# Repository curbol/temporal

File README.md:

# Temporal

A 36-42 key split ergonomic keyboard with wireless support, a breakoff pinky column, and optional encoders in the thumb cluster.

## Design

### Layout

- 36-42 keys depending on configuration:
  - 42/41/40 keys (0/1/2 encoders) with full pinky column
  - 38/37/36 keys (0/1/2 encoders) with breakoff pinky column
- Column stagger and splay on pinky and ring columns

### Hardware

- Kailh Choc v1 or v2 low-profile switches, with optional hotswap sockets
- nice!nano or other Pro Micro compatible microcontrollers
- Optional nice!view display
- Optional EC11/EC12 rotary encoders in thumb cluster (up to 2)
- Wireless with battery support
- Reversible PCB
- 3D-printable cases, with an optional kickstand for tenting

### Tools

- [Ergogen](https://ergogen.ceoloide.com/) generates the layout, PCB, plates, and cases from [ergogen/config.yaml](ergogen/config.yaml)
- [KiCad](https://www.kicad.org/) v10 holds the hand-routed traces; its `pcbnew` API and `kicad-cli` drive the scripted post-processing and the exports

## Firmware

Temporal runs [ZMK](https://zmk.dev/). The shield definition and default keymap live in [temporal-zmk](https://github.com/curbol/temporal-zmk); [curbol/zmk-config](https://github.com/curbol/zmk-config) is a working config that uses it.

## Build Guide

[docs/build-guide.md](docs/build-guide.md) covers assembly and ordering. [docs/bom.md](docs/bom.md) lists every component a full build needs.

## Keycaps

Any Choc-compatible keycap fits. [KLP Lame Keycaps](https://github.com/braindefender/KLP-Lame-Keycaps) are 3D-printable and sculpted; [docs/bom.md](docs/bom.md#switches--keycaps) lists the print quantities for a full build.

## Development

### Prerequisites

- Node.js and npm
- A package manager `make deps` can drive: [Homebrew](https://brew.sh/) on macOS, or `pacman` and `yay` on Arch Linux

### Setup

1. Install dependencies (OpenSCAD, KiCad, zip/unzip, [Maple Mono NF](https://github.com/subframe7536/maple-font) font, and KiCad plugins):

```bash
make deps
```

2. Generate PCBs and cases:

```bash
make gen
```

This will:

- Run Ergogen to generate PCB and case files
- Derive `temporal.json`, the ZMK Studio physical layout, from the same points
- Post-process PCBs (edge cuts, silkscreen widths, ground planes, text keepouts,
  via stitching, zone fills, embedded fonts)
- Configure KiCad project files with defaults from `scripts/kicad_config.yaml`
- Derive the `top_plate_*_stealth` variants from the generated top plates
- Render `assets/preview.svg` and a `pcb.png` per board
- Export gerbers for manufacturing
- Generate the JLCPCB BOM and CPL files in `jlcpcb/`
- Generate STL case files

**Note:** The main `pcbs/temporal/` PCB requires manual steps in KiCad after generation. See [pcbs/temporal/README.md](pcbs/temporal/README.md) for details.

### Verifying

```bash
make check
```

Confirms the sources parse and lint, `ergogen/config.yaml` builds, every committed board passes DRC and carries its own silkscreen font, and the pours in `pcbs/` still match the custom DRC rules and the zone settings. It then regenerates each committed derived artifact and diffs it against what is checked in: `temporal.json`, `jlcpcb/`, the `.kicad_pro` and `.kicad_dru` files, the `top_plate_*_stealth` boards, and the gerber zips. This is what CI runs on every push.

## Influences

Temporal takes influence from:

- [Hillside](https://github.com/mmccoyd/hillside) by mmccoyd
- [TOTEM](https://github.com/GEIGEIGEIST/TOTEM) and [KLOR](https://github.com/GEIGEIGEIST/KLOR) by GEIST
- [TEMPEST](https://github.com/thrly/tempest) by thrly

## Support

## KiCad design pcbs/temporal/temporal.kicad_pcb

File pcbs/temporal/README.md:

# Temporal PCB

`make gen` never overwrites this directory.

## Why

This board is hand-routed in KiCad, and the traces and vias here cannot be
regenerated. The build leaves the `.kicad_pcb` alone and rewrites only the
`.kicad_pro` and `.kicad_dru` beside it.

## How to Regenerate

Delete the folder, then rebuild:

```bash
rm -rf pcbs/temporal
make gen
```

That recreates the directory and a fresh, unrouted board from
`ergogen/config.yaml`.

## Manual Steps in KiCad

After regenerating, route the connections Ergogen does not place. Ground planes,
silkscreen text keepouts, via stitching, and zone fills are all applied by
`make gen` before the board is copied here, so they need no manual work.

## Keeping This Board Current

The post-processing steps run against `ergogen/output/pcbs`, so they reach this
board only when it is regenerated. Editing the `zones`, `via_stitching`, or
`text_keepouts` sections of `scripts/kicad_config.yaml` updates every other board
and leaves this one as it was. `make check` fails when the pour no longer matches
the custom DRC rules; a via stitching or keepout change needs a full regeneration
and a re-route.

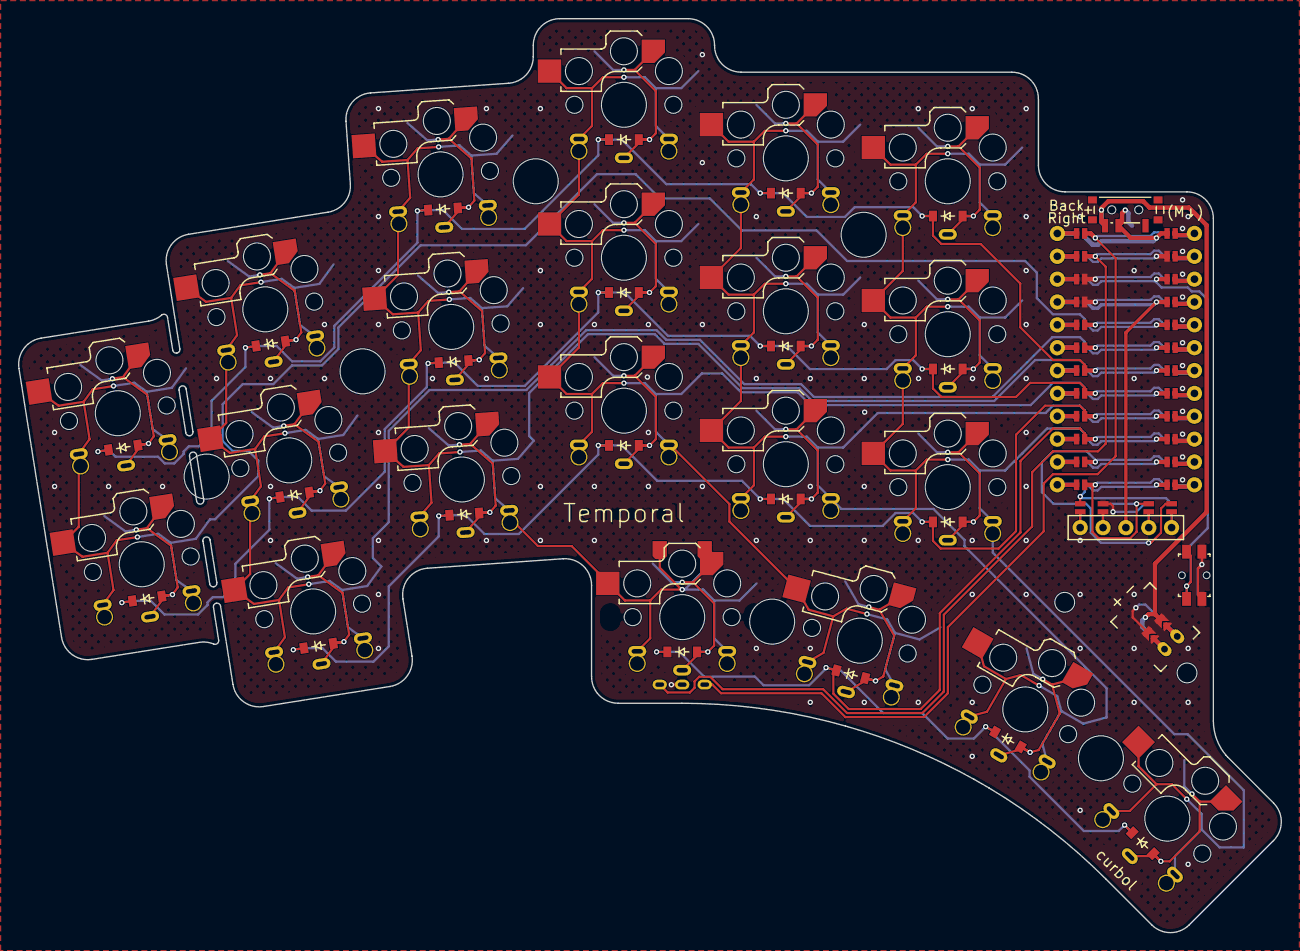
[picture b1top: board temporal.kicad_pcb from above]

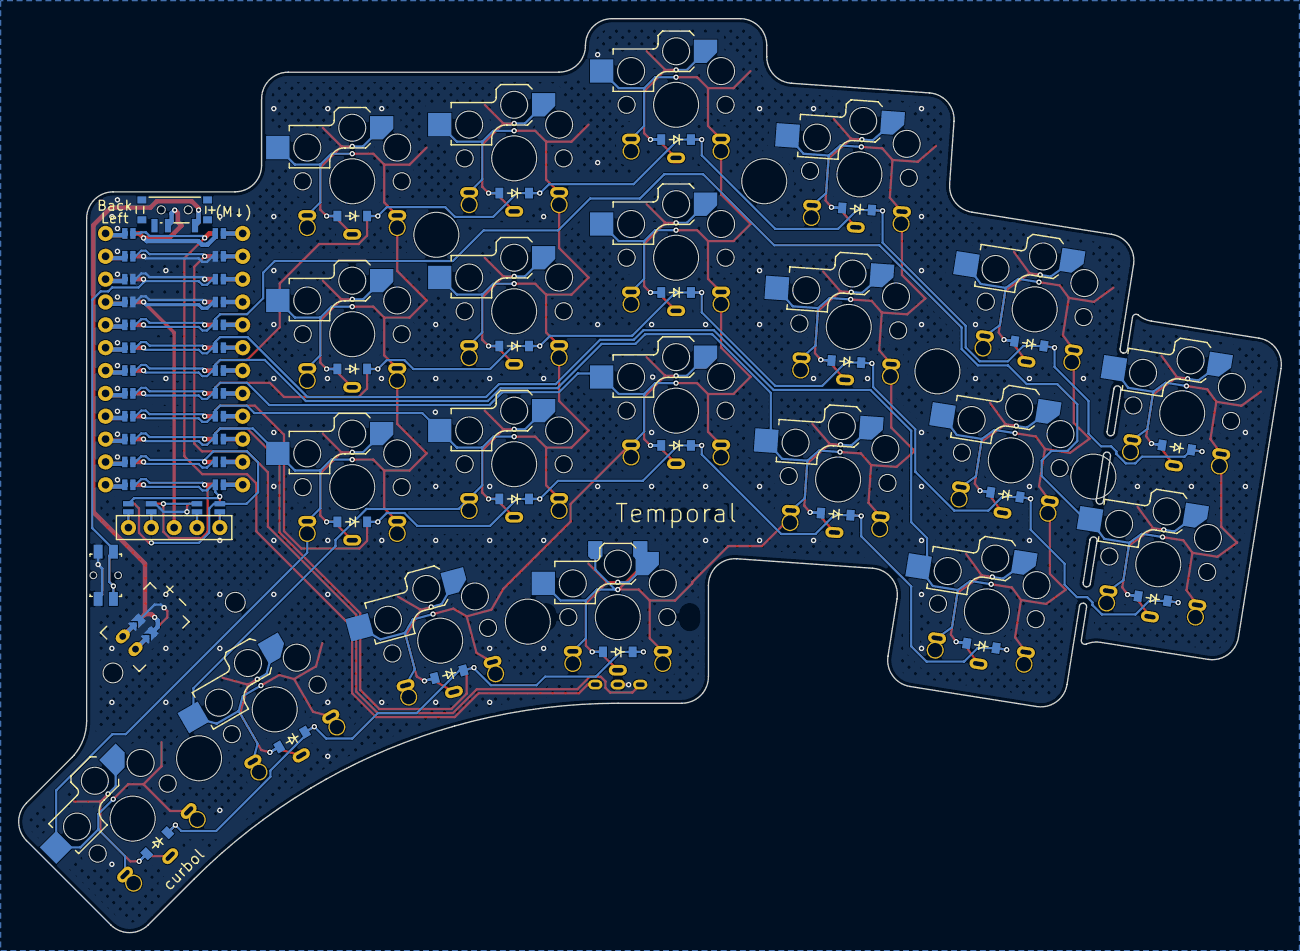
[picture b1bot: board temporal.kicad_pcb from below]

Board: 2 copper layers, 140.4 x 101.6 mm, 56 parts (21 on the bottom side), 47 nets.

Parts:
D1, D2, D3, D4, D5, D6, D7, D8, D9, D10, D11, D12, D13, D14, D15, D16, D17, D18, D19, D20, D21: diode_tht_sod123
DISP1: display_nice_view
JST1: battery_connector_jst_ph_2
MCU1: mcu_nice_nano
MH1, MH2, MH3, MH4, MH5, MH6, MH7, MH8: mounting_hole_npth
PWR1: power_switch_smd_side
RE1: rotary_encoder_ec11_ec12
RST1: reset_switch_smd_side
S1, S2, S3, S4, S5, S6, S7, S8, S9, S10, S11, S12, S13, S14, S15, S16, S17, S18, S19, S20, S21: switch_choc_v1_v2

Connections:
BAT_P: JST1.1, PWR1.1, PWR1.3
CS: DISP1.14, DISP1.24, MCU1.112
DISP1_1: DISP1.1, DISP1.10, DISP1.23
DISP1_2: DISP1.2, DISP1.11, DISP1.22
DISP1_4: DISP1.4, DISP1.12, DISP1.21
DISP1_5: DISP1.5, DISP1.13, DISP1.20
GND: DISP1.15, DISP1.25, JST1.2, MCU1.102, MCU1.121, MCU1.122, RE1.C, RST1.1, RST1.3
JST1_1: JST1.11, JST1.21, JST1.31
JST1_2: JST1.12, JST1.22, JST1.32
MOSI: DISP1.17, DISP1.27, MCU1.114
RAW: MCU1.101, PWR1.2
RST: MCU1.103, RST1.2, RST1.4
SCK: DISP1.16, DISP1.26, MCU1.113
VCC: DISP1.3, MCU1.104
col_extra: MCU1.105, S1.1, S1.2, S2.1, S2.2
col_index: MCU1.109, S12.1, S12.2, S13.1, S13.2, S14.1, S14.2, S20.1, S20.2
col_inner: MCU1.110, S15.1, S15.2, S16.1, S16.2, S17.1, S17.2, S21.1, S21.2
col_middle: MCU1.108, S9.1, S9.2, S10.1, S10.2, S11.1, S11.2, S19.1, S19.2
col_pinky: MCU1.106, S3.1, S3.2, S4.1, S4.2, S5.1, S5.2
col_ring: MCU1.107, RE1.S1, S6.1, S6.2, S7.1, S7.2, S8.1, S8.2, S18.1, S18.2
enc_thumb: D18.2, RE1.S2, S18.1, S18.2
encoder_a: MCU1.123, RE1.A
encoder_b: MCU1.124, RE1.B
extra_home: D1.2, S1.1, S1.2
extra_top: D2.2, S2.1, S2.2
far_thumb: D21.2, S21.1, S21.2
index_bottom: D12.2, S12.1, S12.2
index_home: D13.2, S13.1, S13.2
index_top: D14.2, S14.1, S14.2
inner_bottom: D15.2, S15.1, S15.2
inner_home: D16.2, S16.1, S16.2
inner_top: D17.2, S17.1, S17.2
mid_thumb: D20.2, S20.1, S20.2
middle_bottom: D9.2, S9.1, S9.2
middle_home: D10.2, S10.1, S10.2
middle_top: D11.2, S11.1, S11.2
near_thumb: D19.2, S19.1, S19.2
pinky_bottom: D3.2, S3.1, S3.2
pinky_home: D4.2, S4.1, S4.2
pinky_top: D5.2, S5.1, S5.2
ring_bottom: D6.2, S6.1, S6.2
ring_home: D7.2, S7.1, S7.2
ring_top: D8.2, S8.1, S8.2
row_bottom: D3.1, D6.1, D9.1, D12.1, D15.1, MCU1.116
row_home: D1.1, D4.1, D7.1, D10.1, D13.1, D16.1, MCU1.117
row_thumb: D18.1, D19.1, D20.1, D21.1, MCU1.115
row_top: D2.1, D5.1, D8.1, D11.1, D14.1, D17.1, MCU1.118

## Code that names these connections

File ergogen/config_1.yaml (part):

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          key.column_net: col_extra
        pinky:
          key.stagger: 0.5ky
          key.column_net: col_pinky
        ring:
          key.stagger: 0.35ky
          key.splay: -finger_splay/2
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          include_plated_mounting_holes: false
          include_momentary_switch_pads: true
          smd_momentary_switch: true
          A: encoder_a # Left pin
          C: GND # Center pin
          B: encoder_b # Right pin
          S1: col_ring # Switch pin 1
          S2: encoder_thumb # Switch pin 2

      mcu:
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          P15: col_index
          P18: col_middle
          P19: col_ring
          P20: col_pinky
          P21: col_extra
          # Encoder (using available pins)
          P0: encoder_a
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
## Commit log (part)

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2025-11-01 move pcb project files
2025-11-01 add makefile and package.json
2025-11-01 fix graphic
2025-11-01 move solar graphic
2025-11-01 case and backplate updates
2025-11-02 move case stls
2025-11-02 update m2 socket size
2025-11-08 working on new version with more splay
2025-11-10 fix holes and cuts
2025-11-10 move mounting holes
2025-11-12 update generated files
2025-11-12 working on new case
2025-11-12 fix curve on case
2025-11-14 working on 4 boards
2025-11-16 fix cutouts and preview
2025-11-16 fix m2 nut cutout
2025-11-16 folder cleanup
2025-11-17 update footprints
2025-11-17 cleanup
2025-11-17 ignore ergogen outputs
2025-11-17 small silkscreen change
2025-11-17 update neuron silkscreen
2025-11-17 simplify
2025-11-17 update brain svg
2025-11-18 Add scripts
2025-11-18 brain updates
2025-11-18 update silkscreens
2025-11-18 Add centralized KiCad defaults configuration system
    This commit implements a centralized configuration system for KiCad project defaults,
    allowing easy management and regeneration of .kicad_pro files.
    Changes:
    - Add config/kicad_defaults.yaml: Central configuration for all KiCad defaults
    (via sizes, trace widths, clearances, zone settings, etc.)
    - Add scripts/setup_kicad_project.py: Script to generate/update .kicad_pro files
2025-11-18 Fix track width to match README manufacturing specs
    Update default track_width from 0.2mm to 0.25mm to match the
    manufacturing specifications documented in pcbs/README.md.
    Also add note about custom trace widths for power (0.375mm) and
    battery (0.5mm) nets that should be set up as separate net classes.
    Changes:
    - config/kicad_defaults.yaml: Update track_width to 0.25mm
2025-11-18 Simplify ergogen config using YAML features
    - Add variables to units section (board_hole_radius, plate_thickness, mcu_pin_spacing)
    - Create YAML anchor for hole locations to eliminate ~40 lines of repetition
    - Consolidate _board_holes, _m2_insert_outer_posts, and _m2_insert_inner_posts
    - Replace magic numbers with named constants throughout config
    - Fix typo: 'thmub' → 'thumb' in comment
    Reduces config from ~1384 to ~1334 lines with no logic changes.
2025-11-18 refinements
2025-11-18 Convert Python scripts to JavaScript/Node.js
    Replace all Python scripts with JavaScript equivalents to use a single
    toolchain (Node.js) across the entire project, eliminating the need for
    Python dependencies.
    Changes:
    - scripts/fix_edge_cuts.js: Convert from Python, uses glob for file finding
    - scripts/add_ground_planes.js: Convert from Python, uses js-yaml for config
2025-11-19 Change hatch smoothing level to 1 (light smoothing)
    Update hatch_smoothing_level from 0 (none) to 1 (light) for better
    hatch pattern appearance in ground plane fills.
    Changes:
    - config/kicad_defaults.yaml: Set hatch_smoothing_level to 1
    - scripts/add_ground_planes.js: Update fallback default to match
2025-11-19 Claude/kicad defaults storage 017 ue tvd9sdqibd hal mo4 v fb (#1)
    * Add centralized KiCad defaults configuration system
2025-11-19 Fix keepout zone rotation by embedding zones in footprints
    The previous fix (cf06caa) attempted to use p.r for rotation, but the
    fundamental issue was that keepout zones were generated as separate
    board-level objects with absolute coordinates. This meant they would
    not rotate when the footprint was rotated in KiCad.
    Root cause:
    - Zones were generated outside the footprint definition
2025-11-19 Improve documentation quality and remove TEMPEST references
    - Remove vague "WORK IN PROGRESS" message from README
    - Remove broken image references (no images/ directory exists)
    - Fix incorrect GitHub badge that pointed to wrong repo
    - Update all TEMPEST references to TEMPORAL (except proper attributions)
    - Fix file paths in build-guide.md (temporal.zip not tempest_v2_gerbers.zip)
    - Improve pcbs/README.md with better structure and information
2025-11-19 Regenerate build artifacts after JSCAD CLI fix
    After fixing the @jscad/cli version issue, ran make gen to regenerate
    all build artifacts:
    - Regenerated STL case files using the working @jscad/cli@1
    - Added new PCB files for all plate variants
    - Removed gerber zips (will be regenerated when kicad-cli is available)
    - Updated KiCad project configurations
2025-11-19 package lock
2025-11-19 formatting
2025-11-19 format defaults
2025-11-19 remove knockout
2025-11-19 Update mirrored cases to support 4 case variations
    Updated the mirror target in Makefile to generate mirrored versions
    for all 4 case variations (temporal_38, temporal_40, temporal_42,
    temporal_44) instead of the outdated 2 variations (temporal,
    temporal_small).
2025-11-19 Transform knockout zone coordinates to absolute board position
    The keepout zones were appearing at absolute 0,0 (top-left corner in
    KiCad) instead of being positioned relative to their silkscreens. This
    was because zones in KiCad always use absolute board coordinates, even
    when embedded inside footprint definitions.
    Root cause:
    - The previous fix (commit 7731db2) centered the polygon at origin
2025-11-19 Use p.r (Ergogen rotation parameter) instead of rotation from p.at
    The knockout zones were still not rotating correctly because we were
    using rotation extracted from p.at instead of using Ergogen's p.r
    parameter directly.
    Root cause:
    - p.at may not contain rotation, or contains a different rotation value
    - Ergogen provides p.r as the authoritative rotation parameter
2025-11-19 Use footprint-relative coordinates for zones - let KiCad apply rotation
    The knockout zones were not rotating because we were using absolute board
    coordinates which don't get rotated by KiCad when the footprint is rotated.
    Root cause discovered through debug logging:
    - Zones embedded in footprints use the footprint's coordinate system
    - When we transformed to absolute coordinates, KiCad didn't apply the
    footprint's rotation to the zone
2025-11-19 Apply full rotation+translation transform to test if zones need it
2025-11-19 Test negative rotation - apply rotation in opposite direction
    User feedback indicates we're "one rotation off", suggesting the rotation
    direction might be reversed. Testing with -rotation instead of +rotation
    to see if the coordinate system or transformation has opposite handedness.
    Changes:
    - Using -rotation in transformPolygon calls
    - This rotates clockwise instead of counter-clockwise (or vice versa)
2025-11-19 Clean up debug logging and fix brain polygon wrong line connection
    Changes:
    1. Removed all debug console.log statements from neuron.js and brain.js
    2. Fixed brain polygon issue where extra points after the closing point
    were creating an erroneous line connection on the right side
    3. Removed 10 extra polygon points (lines 6866-6875) that were causing
    a 37.93 unit jump from (29.52, 29.44) to (40.95, -6.73)
2025-11-19 Revert neuron polygon change - restore necessary points
    The previous commit removed 4 points that were actually needed for the
    neuron shape, causing a cut out. Restoring the points:
    - (xy 8.862272081670532 -4.648682160791666)
    - (xy 8.932737899378868 -4.64878600975)
    - (xy 9.004900754587197 -4.652767327458332)
    - (xy 9.004910015003865 -4.652773148291666)
2025-11-19 update makefile
2025-11-19 fix plate holes
2025-11-20 update brain
2025-11-20 working on updating mounting holes
2025-11-20 add extra mount holes
2025-11-20 updated silkscreens
2025-11-21 position neuron
2025-11-21 add readme to pcbs/temparal
2025-11-21 mov thumb in tiny bit. fix posts.
2025-11-21 fill unused post holes and rename
2025-11-21 add manual steps to readme
2025-11-22 positioning changes
2025-11-22 pos reset and pwr
2025-11-24 temporal keyboard
2025-11-24 create image for all pcbs
2025-11-24 update reset footprint
2025-11-25 add support for reset switches with bosses
2025-11-25 update gen files
2025-11-25 reorder gen steps
2025-11-25 automate via stitching
2025-11-25 fix via stitching count
2025-11-25 add create keepout zones
2025-11-26 footprint cleanup
2025-11-26 small change to neuron
2025-11-26 format kicad project numbers
2025-11-26 update pcbs
2025-11-26 kicad config fixes
2025-11-26 revert number formatting
2025-11-26 increase mcu text scpacing
2025-11-26 support keepouts for text inside footprints
2025-11-27 change via size, move sig
2025-11-27 fix trace from diode to hotswap
2025-11-27 working on traces
2025-11-27 update display footprint
2025-11-29 traces finished
2025-11-29 update preview
2025-11-29 update hole4
2025-11-29 adjust text position
2025-11-30 add bom and cpl generation
2025-11-30 add note on jlc3dp material
2025-12-01 update case cutouts
2025-12-02 add script to generate layout
2025-12-12 several layout changes
2025-12-12 refine hole positions
2025-12-13 minor cleanup
2025-12-13 swap power and reset
2025-12-13 update docs
2025-12-14 remove silkscreens, move text, increase fillet
2025-12-14 increase break cut size and update case side cutouts
2025-12-15 Add kickstand case versions
2025-12-15 fix case kickstand depth
2025-12-15 create mirrors of kickstand cases
2025-12-15 improve top_plate smoothing
2025-12-15 script improvements
2025-12-15 improve build output
2025-12-16 update via positions
2025-12-16 separate switch vias
2025-12-18 update switch recommendation
2025-12-18 finished routing traces
2025-12-19 add outlines with mirrored cutouts
2025-12-19 update how mirroring is done
2025-12-19 remove test line
2025-12-19 update depths
2025-12-20 add fillet to cutouts
2025-12-20 scale arc segments with radius
2025-12-20 more scaling at lower radius
2025-12-20 simplify arc resolution
2025-12-20 output time to complete build
2025-12-21 update kickstand
2025-12-23 fix encoder net
2025-12-25 finish traces
2025-12-26 remove sockets from jlcpcb bom
    jlcpcb is not able to add hotswap sockets.
2025-12-26 remove sockets for JLC PCBA
2025-12-27 Update Normal part 2 to Thumbs in BOM
2025-12-28 Change source link for M2 Heat Set Inserts
    Updated source link for M2 Heat Set Inserts.
2026-01-09 fix layout script
2026-01-09 fix col numbers
2026-01-12 slightly increase cutout sizes
2026-01-12 make plug a square
2026-01-12 Add resistor pads
2026-01-13 update resistor pad size
2026-01-13 add switch solder holes
2026-01-14 move curbol down a bit
2026-01-14 remove duplicate traces
2026-01-14 case refinements
2026-01-14 rename to correct keycounts
2026-01-15 rearrange preview
2026-01-15 add mcu catch and refactor mcu_area vars
2026-01-16 rename left and right parts
2026-01-16 refactor choc post outlines
2026-01-16 update to new wording
2026-01-17 small refactors
2026-01-17 revert mirroring to OpenSCAD
2026-01-18 romove some expands
2026-01-18 simplify socket cutouts
2026-01-18 fix geometry
2026-01-18 first draft of build guide
2026-01-19 Guide refinements
2026-01-19 small updates
2026-01-19 add images to bom
2026-01-19 add flux pen image
2026-01-19 add images
2026-01-19 update sources
2026-01-19 reorder
2026-01-20 add some tips
2026-01-20 add usernames
2026-01-20 change to collective name
2026-01-20 reduce catch size
2026-01-20 increase catch size
2026-01-21 refactor case posts
2026-01-21 refactor socket cutout
2026-01-21 rename resolution
2026-01-22 use pymeshfix instead of admesh
2026-01-22 go back to openscad
2026-01-22 move anchor
2026-01-25 Reorder sources for Choc v1 Switches in BOM
2026-01-25 add display socket
2026-01-25 update image

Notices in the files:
README.md:
License: CERN-OHL-P-2.0
